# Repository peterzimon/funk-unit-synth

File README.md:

# Shmøergh Funk Live One — 6 voice paraphonic synthesizer

Shmøergh Funk Live One is a 6 voice (mostly) digitally controlled paraphonic
analog synthesizer. Its purposefully built with limitations so it's great for
live performances with quick changes in settings without presets or menu diving. It
has a lot of simple but effective ways to modulate the filter cutoff which makes
it great for funk performances. Because of its simplicity it's also cool to get
started with synthesis.

**Status:** WORK IN PROGRESS

**Latest version:** 1.1

## Features

- 6 voices (DCOs) controlled by a Raspberry Pi Pico
- Sawtooth, square, narrow pulse and fixed rate pulse with modulated square waveforms
- Analog signal path
- External filter connection with selectable various modulation sources (envelope, velocity, analog LFO, modwheel, keyboard tracking). Steiner-Parker
filter schematics and PCB is included
- 12bit digital ADSR with simplified envelope controls
- Built-in analog VCA with optional external VCA connections
- Monophonic, 3-voice unison with detune and 6-voice paraphonic modes
- MIDI input
- Eurorack compatible PCB sizing

Note: schematics does not include power supply

## References

- [Polykit DCO design](https://github.com/polykit/pico-dco)
- [The design of the Roland Juno synthesizes](https://blog.thea.codes/the-design-of-the-juno-dco/)
- [Steiner-Parker Filter](https://yusynth.net/Modular/EN/STEINERVCF/index-v2.html)

## License & info

Version: 1.1.0
Author: Peter Zimon
Copyright: 2023
Licence: MIT

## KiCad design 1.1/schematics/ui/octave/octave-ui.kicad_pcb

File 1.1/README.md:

# V1.1

- Added DC blocking to mixer inputs to avoid shifting waveforms by f=0Hz frequency DCOs
- Decreased sawtooth and square mixer amplification to avoid distortion

## License & info

Version: 1.0.0
Author: Peter Zimon
Copyright: 2023
Licence: MIT

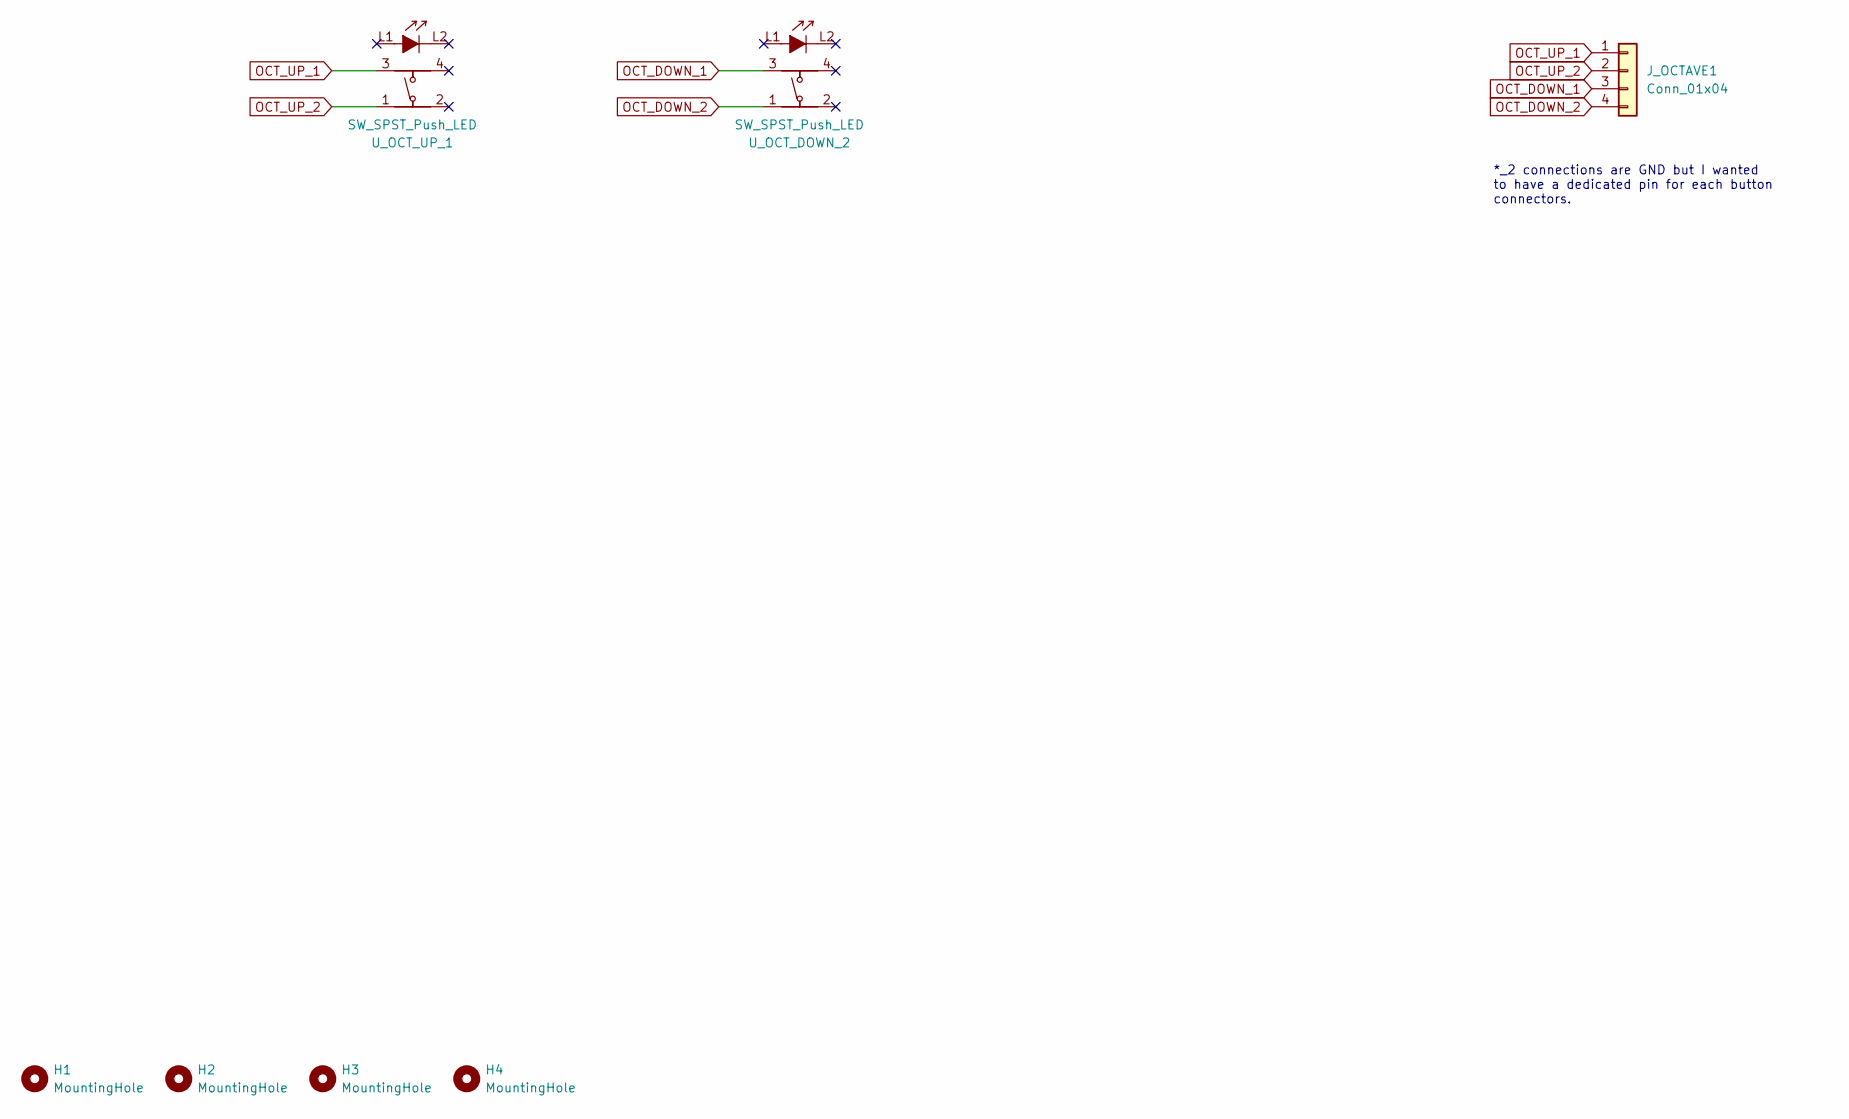
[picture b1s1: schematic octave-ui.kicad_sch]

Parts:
H1, H2, H3, H4: MountingHole; MountingHole_4mm
J_OCTAVE1: Conn_01x04; NSL25_01x04_Vertical
U_OCT_DOWN_2: SW_SPST_Push_LED; SPST_Narrow_Circular_Pushbutton_LED
U_OCT_UP_1: SW_SPST_Push_LED; SPST_Narrow_Circular_Pushbutton_LED

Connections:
OCT_DOWN_1: J_OCTAVE1.3, U_OCT_DOWN_2.3
OCT_DOWN_2: J_OCTAVE1.4, U_OCT_DOWN_2.1
OCT_UP_1: J_OCTAVE1.1, U_OCT_UP_1.3
OCT_UP_2: J_OCTAVE1.2, U_OCT_UP_1.1

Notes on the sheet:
*_2 connections are GND but I wanted to have a dedicated pin for each button connectors.

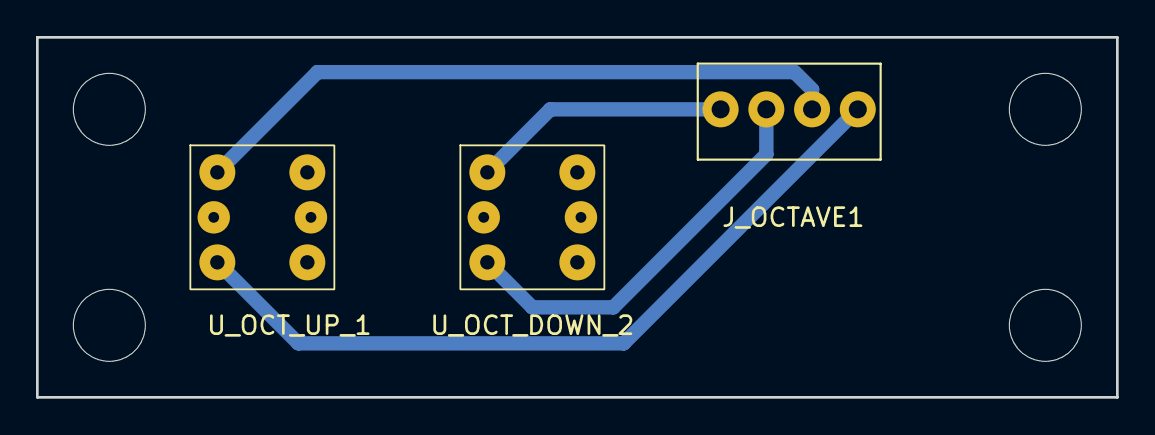
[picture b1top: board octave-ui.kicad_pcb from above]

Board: 2 copper layers, 60.0 x 20.0 mm, 7 parts (0 on the bottom side), 4 nets.

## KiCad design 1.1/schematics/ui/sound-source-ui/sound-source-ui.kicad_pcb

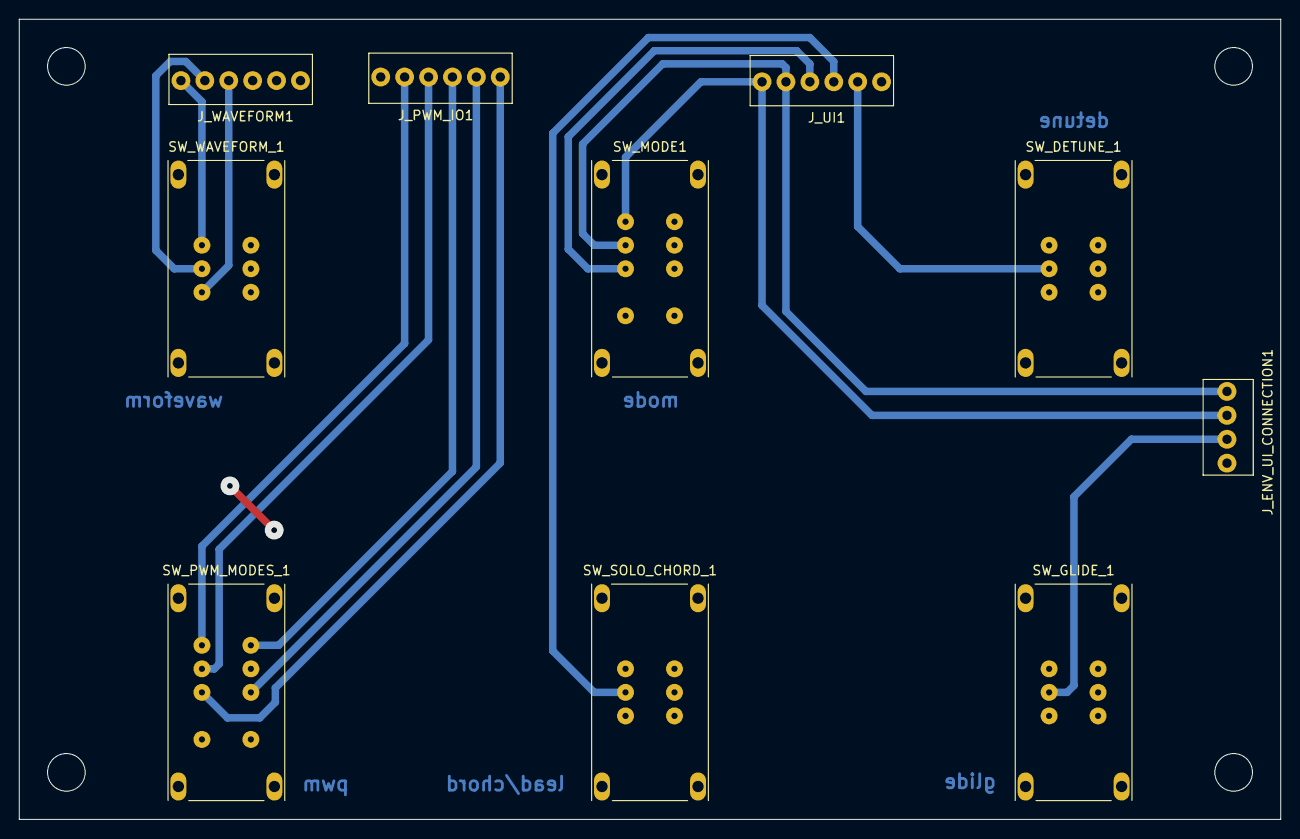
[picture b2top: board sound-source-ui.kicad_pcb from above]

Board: 2 copper layers, 134.0 x 85.0 mm, 14 parts (0 on the bottom side), 15 nets.

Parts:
H1, H2, H3, H4: MountingHole; MountingHole_4mm
J_ENV_UI_CONNECTION1: Conn_01x04; NSL25_01x04_Vertical
J_PWM_IO1: Conn_01x06; NSL25_01x06_Vertical
J_UI1: Conn_01x06; NSL25_01x06_Vertical
J_WAVEFORM1: Conn_01x03; NSL25_01x06_Vertical
SW_DETUNE_1: SW_DPDT_x2; DPDT Korg Style Switch
SW_GLIDE_1: SW_DPDT_x2; DPDT Korg Style Switch
SW_MODE1: SW_DP3T; DP3T Korg Style Switch
SW_PWM_MODES_1: SW_DP3T; DP3T Korg Style Switch
SW_SOLO_CHORD_1: SW_DPDT_x2; DPDT Korg Style Switch
SW_WAVEFORM_1: SW_DPDT_x2; DPDT Korg Style Switch

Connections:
1.5V: J_ENV_UI_CONNECTION1.1, J_UI1.2, SW_MODE1.2
+3.3V: J_ENV_UI_CONNECTION1.2, J_UI1.1, SW_MODE1.1
DETUNE: J_UI1.5, SW_DETUNE_1.3 (B)
GLIDE: J_ENV_UI_CONNECTION1.3, SW_GLIDE_1.3 (B)
GND: J_ENV_UI_CONNECTION1.4, J_PWM_IO1.6, J_UI1.6, SW_DETUNE_1.5 (C), SW_GLIDE_1.5 (C), SW_MODE1.4, SW_PWM_MODES_1.4, SW_PWM_MODES_1.6, SW_PWM_MODES_1.8, SW_SOLO_CHORD_1.5 (C)
MODE: J_UI1.3, SW_MODE1.3
PULSE_WIDTH: J_PWM_IO1.1, SW_PWM_MODES_1.3
PWM_LFO: J_PWM_IO1.3, SW_PWM_MODES_1.5
PWM_LFO_BIAS: J_PWM_IO1.5, SW_PWM_MODES_1.1
PWM_NARROW_BIAS: J_PWM_IO1.4, SW_PWM_MODES_1.2
PWM_OUT: J_PWM_IO1.2, SW_PWM_MODES_1.7
SAW_IN: J_WAVEFORM1.3, SW_WAVEFORM_1.5 (C)
SOLO_CHORD: J_UI1.4, SW_SOLO_CHORD_1.3 (B)
SQR_IN: J_WAVEFORM1.1, SW_WAVEFORM_1.1 (A)
WAVEFORM_OUT: J_WAVEFORM1.2, SW_WAVEFORM_1.3 (B)

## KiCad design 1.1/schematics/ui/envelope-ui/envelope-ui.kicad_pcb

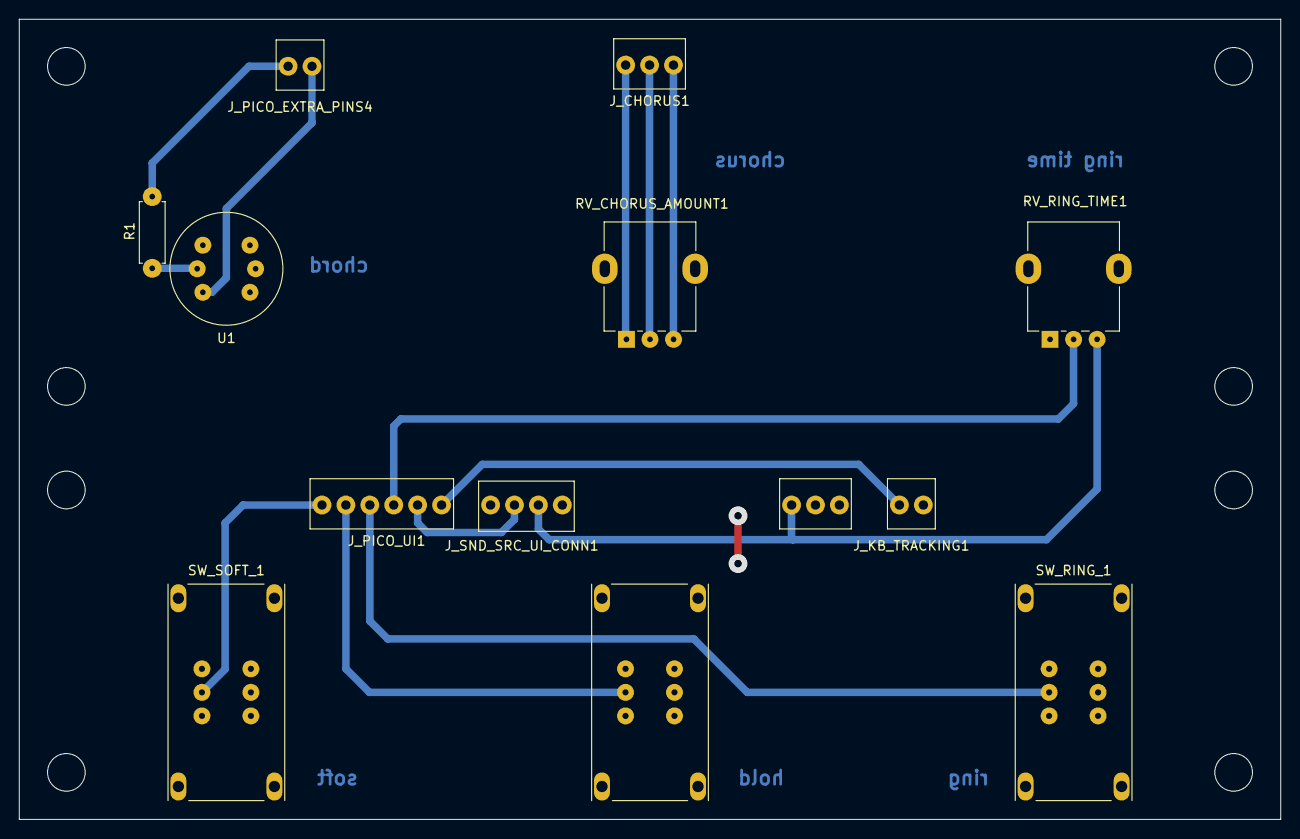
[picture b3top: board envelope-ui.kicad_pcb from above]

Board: 2 copper layers, 134.0 x 85.0 mm, 21 parts (0 on the bottom side), 14 nets.

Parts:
H1, H2, H3, H4, H5, H6, H7, H8: MountingHole; MountingHole_4mm
J_CHORUS1: Conn_01x03; NSL25_01x03_Vertical
J_KB_TRACKING1: Conn_01x02; NSL25_01x02_Vertical
J_PICO_EXTRA_PINS4: Conn_01x02; NSL25_01x02_Vertical
J_PICO_UI1: Conn_01x06; NSL25_01x06_Vertical
J_PWR1: Conn_01x03; NSL25_01x03_Vertical
J_SND_SRC_UI_CONN1: Conn_01x04; NSL25_01x04_Vertical
R1: R; R_Axial_DIN0207_L6.3mm_D2.5mm_P7.62mm_Horizontal
RV_CHORUS_AMOUNT1: 100k; Potentiometer_Alpha_RD901F-40-00D_Single_Vertical
RV_RING_TIME1: 100k; Potentiometer_Alpha_RD901F-40-00D_Single_Vertical
SW_HOLD_1: SW_DPDT_x2; DPDT Korg Style Switch
SW_RING_1: SW_DPDT_x2; DPDT Korg Style Switch
SW_SOFT_1: SW_DPDT_x2; DPDT Korg Style Switch
U1: SW_SPST_Push_LED; SPST_Circular_Pushbutton_LED

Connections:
+3.3V: J_PWR1.1, J_SND_SRC_UI_CONN1.2, RV_RING_TIME1.3
CHORD_BTN: J_PICO_EXTRA_PINS4.2, U1.3
CHORD_LED: J_PICO_EXTRA_PINS4.1, R1.1
CHORUS_1: J_CHORUS1.1, RV_CHORUS_AMOUNT1.1
CHORUS_2: J_CHORUS1.2, RV_CHORUS_AMOUNT1.2
CHORUS_3: J_CHORUS1.3, RV_CHORUS_AMOUNT1.3
GLIDE: J_PICO_UI1.5, J_SND_SRC_UI_CONN1.3
GND: J_KB_TRACKING1.2, J_PWR1.2, J_PWR1.3, J_SND_SRC_UI_CONN1.4, RV_RING_TIME1.1, SW_HOLD_1.5 (C), SW_RING_1.5 (C), SW_SOFT_1.5 (C), U1.1, U1.L2
HOLD: J_PICO_UI1.2, SW_HOLD_1.3 (B)
KB_TRACKING: J_KB_TRACKING1.1, J_PICO_UI1.6
unnamed: R1.2, U1.L1
RING: J_PICO_UI1.3, SW_RING_1.3 (B)
RING_TIME: J_PICO_UI1.4, RV_RING_TIME1.2
SOFT: J_PICO_UI1.1, SW_SOFT_1.3 (B)

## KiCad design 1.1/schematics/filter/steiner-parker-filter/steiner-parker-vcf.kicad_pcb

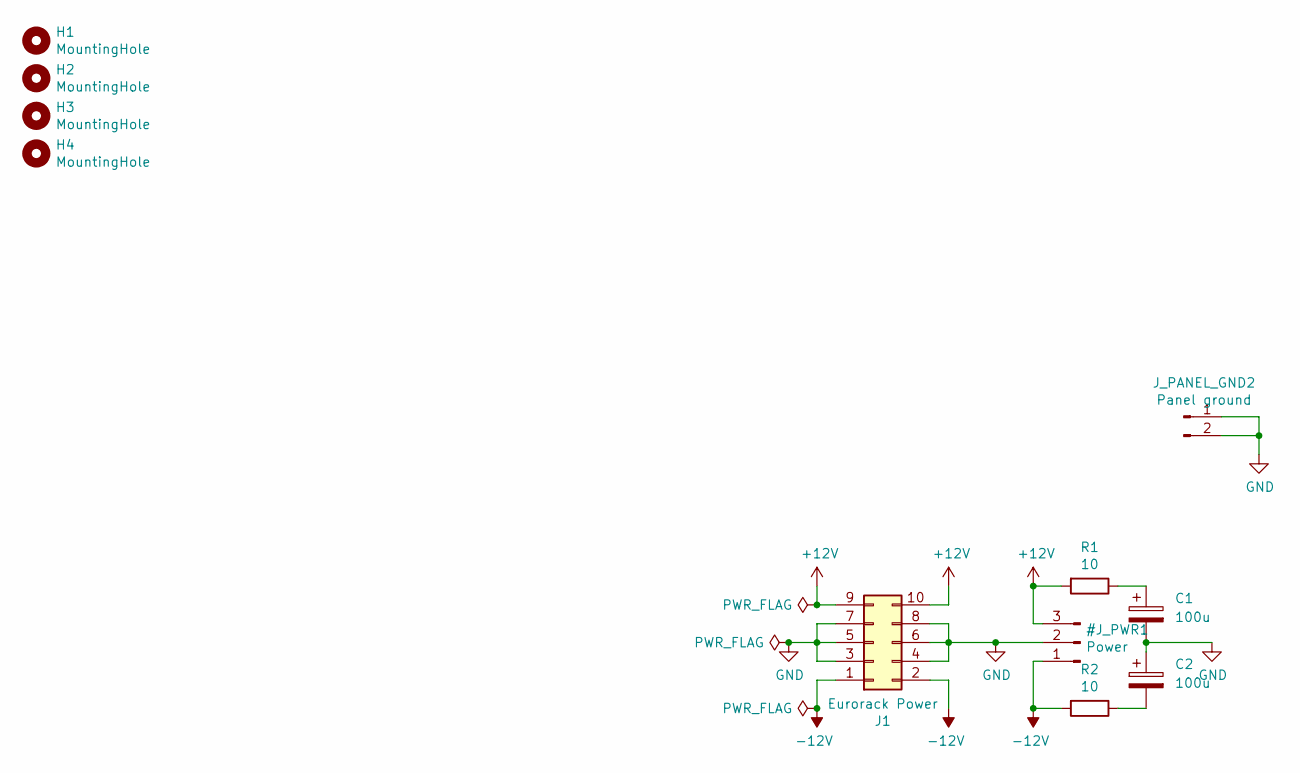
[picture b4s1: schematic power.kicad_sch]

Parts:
C1, C2: 100u; CP_Radial_D6.3mm_P2.50mm
H1, H2, H3, H4: MountingHole; MountingHole_3mm_Pad
J1: Eurorack Power; IDC-Header_2x05_P2.54mm_Vertical
J_PANEL_GND2: Panel ground; NSL25_01x02_Vertical
R1, R2: 10; R_Axial_DIN0207_L6.3mm_D2.5mm_P7.62mm_Horizontal

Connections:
unnamed: C1.1, R1.1
unnamed: C2.2, R2.1

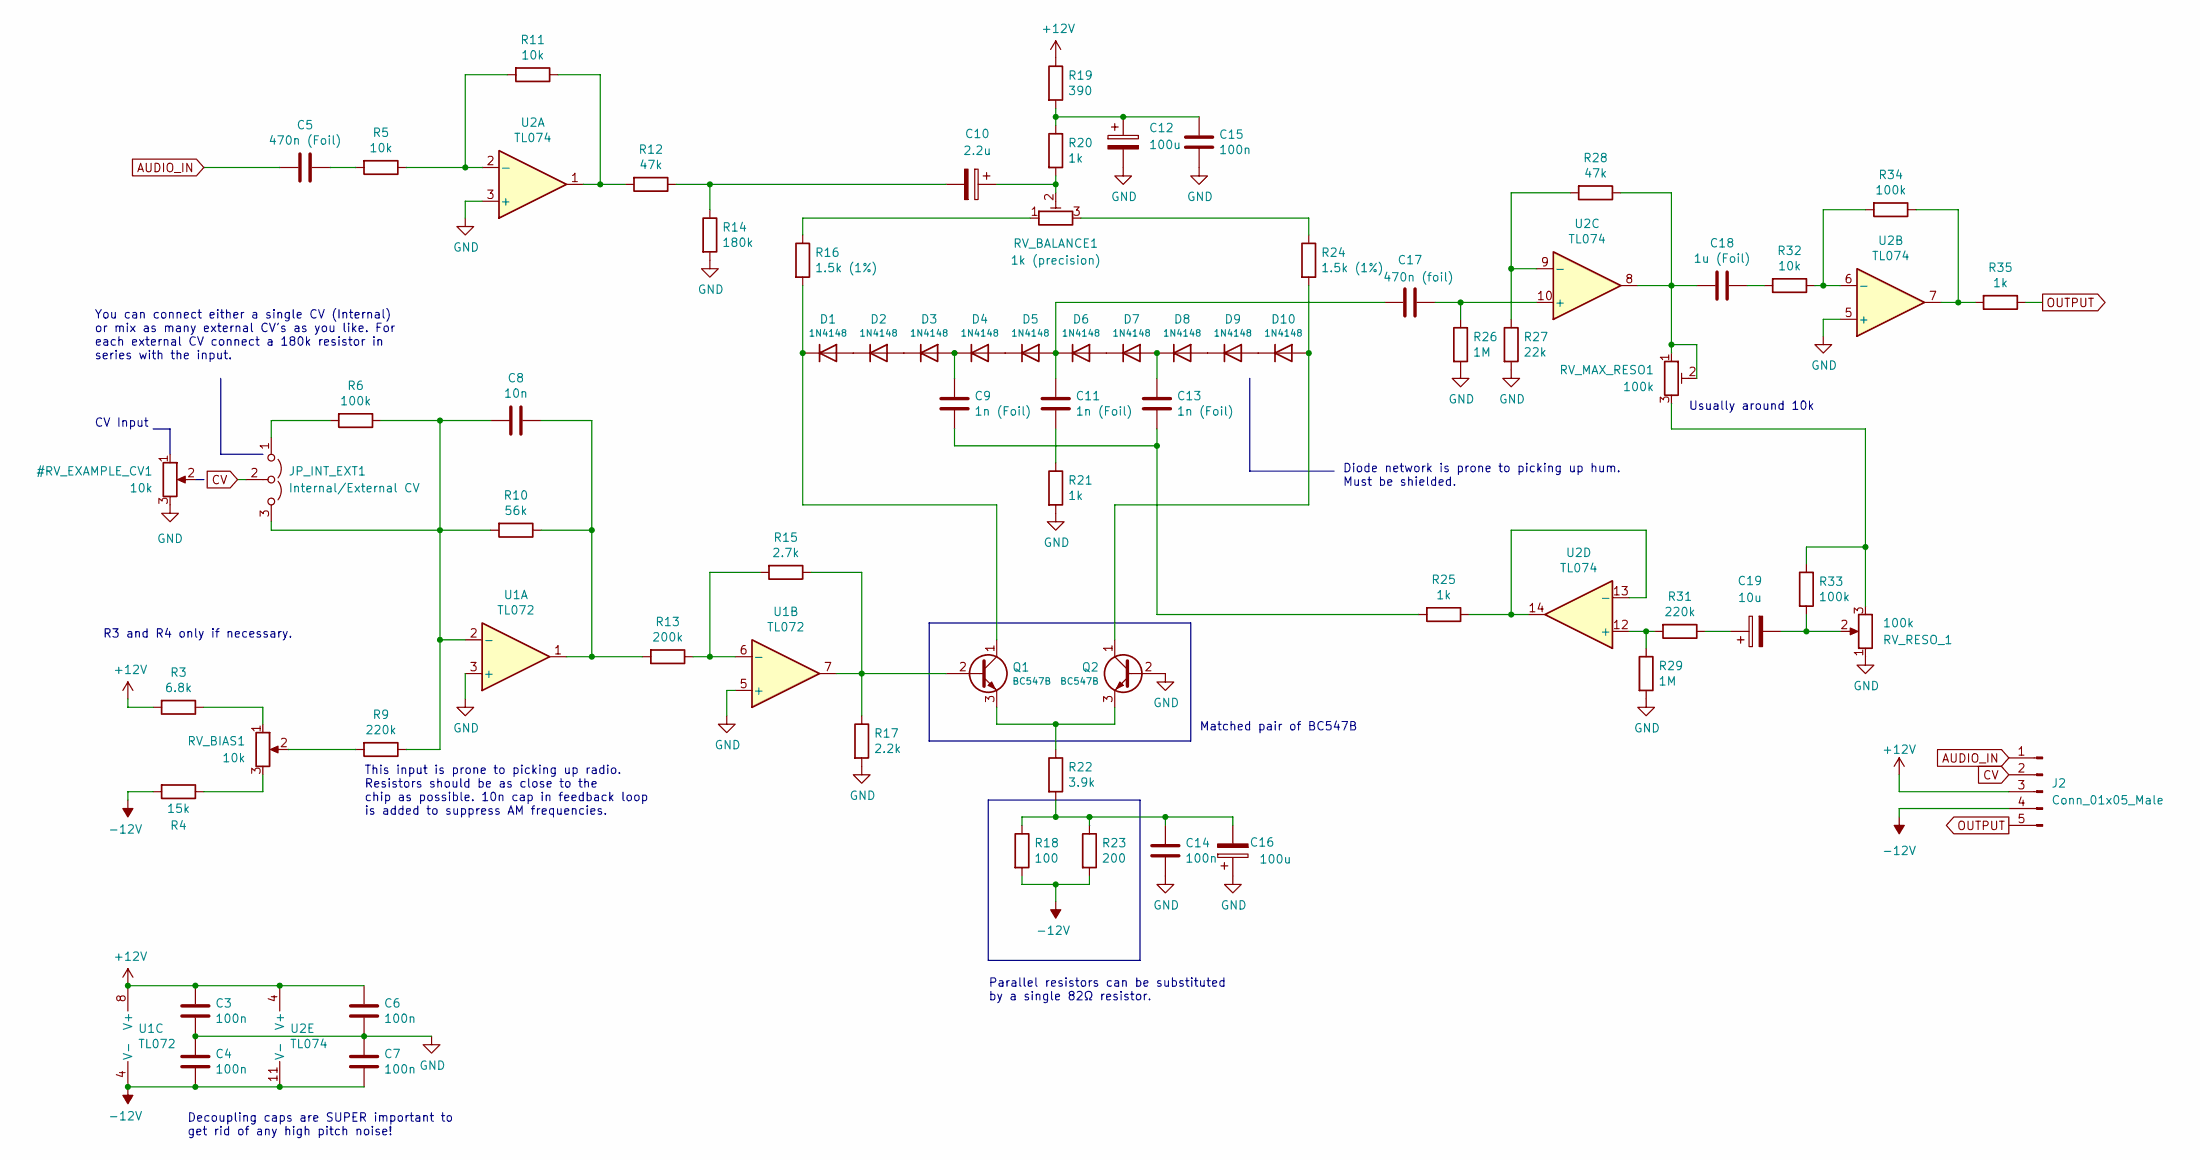
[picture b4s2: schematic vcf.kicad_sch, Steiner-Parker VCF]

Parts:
C3, C4, C6, C7, C14, C15: 100n; C_Disc_D3.0mm_W2.0mm_P2.50mm
C5: 470n (Foil); C_Rect_L7.0mm_W2.5mm_P5.00mm
C8: 10n; C_Disc_D3.0mm_W2.0mm_P2.50mm
C9, C11, C13: 1n (Foil); C_Rect_L7.0mm_W2.5mm_P5.00mm
C10: 2.2u; CP_Radial_D6.3mm_P2.50mm
C12, C16: 100u; CP_Radial_D6.3mm_P2.50mm
C17: 470n (foil); C_Rect_L7.0mm_W2.5mm_P5.00mm
C18: 1u (Foil); C_Rect_L7.0mm_W4.5mm_P5.00mm
C19: 10u; CP_Radial_D6.3mm_P2.50mm
D1, D2, D3, D4, D5, D6, D7, D8, D9, D10: 1N4148; D_DO-35_SOD27_P7.62mm_Horizontal
J2: Conn_01x05_Male; NSL25_01x05_Vertical
JP_INT_EXT1: Internal/External CV; PinSocket_1x03_P2.54mm_Vertical
Q1, Q2: BC547B; TO-92_Inline_Wide
R3: 6.8k; R_Axial_DIN0207_L6.3mm_D2.5mm_P7.62mm_Horizontal
R4: 15k; R_Axial_DIN0207_L6.3mm_D2.5mm_P7.62mm_Horizontal
R5, R11, R32: 10k; R_Axial_DIN0207_L6.3mm_D2.5mm_P7.62mm_Horizontal
R6, R33, R34: 100k; R_Axial_DIN0207_L6.3mm_D2.5mm_P7.62mm_Horizontal
R9, R31: 220k; R_Axial_DIN0207_L6.3mm_D2.5mm_P7.62mm_Horizontal
R10: 56k; R_Axial_DIN0207_L6.3mm_D2.5mm_P7.62mm_Horizontal
R12, R28: 47k; R_Axial_DIN0207_L6.3mm_D2.5mm_P7.62mm_Horizontal
R13: 200k; R_Axial_DIN0207_L6.3mm_D2.5mm_P7.62mm_Horizontal
R14: 180k; R_Axial_DIN0207_L6.3mm_D2.5mm_P7.62mm_Horizontal
R15: 2.7k; R_Axial_DIN0207_L6.3mm_D2.5mm_P7.62mm_Horizontal
R16, R24: 1.5k (1%); R_Axial_DIN0207_L6.3mm_D2.5mm_P7.62mm_Horizontal
R17: 2.2k; R_Axial_DIN0207_L6.3mm_D2.5mm_P7.62mm_Horizontal
R18: 100; R_Axial_DIN0207_L6.3mm_D2.5mm_P7.62mm_Horizontal
R19: 390; R_Axial_DIN0207_L6.3mm_D2.5mm_P7.62mm_Horizontal
R20, R21, R25, R35: 1k; R_Axial_DIN0207_L6.3mm_D2.5mm_P7.62mm_Horizontal
R22: 3.9k; R_Axial_DIN0207_L6.3mm_D2.5mm_P7.62mm_Horizontal
R23: 200; R_Axial_DIN0207_L6.3mm_D2.5mm_P7.62mm_Horizontal
R26, R29: 1M; R_Axial_DIN0207_L6.3mm_D2.5mm_P7.62mm_Horizontal
R27: 22k; R_Axial_DIN0207_L6.3mm_D2.5mm_P7.62mm_Horizontal
RV_BALANCE1: 1k (precision); Potentiometer_Bourns_3296W_Vertical
RV_BIAS1: 10k; Potentiometer_Runtron_RM-065_Vertical
RV_MAX_RESO1: 100k; Potentiometer_Runtron_RM-065_Vertical
RV_RESO_1: 100k; NSL25_01x03_Vertical
U1: TL072; DIP-8_W7.62mm_LongPads
U2: TL074; DIP-14_W7.62mm_LongPads

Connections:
AUDIO_IN: C5.2, J2.1
CV: J2.2, JP_INT_EXT1.2 (C)
unnamed: C5.1, R5.2
unnamed: C8.1, R10.1, R13.2, U1.1
unnamed: C10.1, R20.2, RV_BALANCE1.2
unnamed: C10.2, R12.1, R14.1
unnamed: C11.2, R21.1
unnamed: C12.1, C15.1, R19.2, R20.1
unnamed: C9.2, C13.2, R25.2
unnamed: C14.1, C16.2, R18.1, R22.2, R23.1
unnamed: C18.1, R32.2
unnamed: C18.2, R28.1, RV_MAX_RESO1.1, RV_MAX_RESO1.2, U2.8
unnamed: C19.1, R31.1
unnamed: C19.2, R33.2, RV_RESO_1.2
unnamed: D1.2 (A), D2.1 (K)
unnamed: D1.1 (K), Q1.1 (C), R16.2
unnamed: D2.2 (A), D3.1 (K)
unnamed: C9.1, D3.2 (A), D4.1 (K)
unnamed: D4.2 (A), D5.1 (K)
unnamed: C11.1, C17.2, D5.2 (A), D6.1 (K)
unnamed: D6.2 (A), D7.1 (K)
unnamed: C13.1, D7.2 (A), D8.1 (K)
unnamed: D8.2 (A), D9.1 (K)
unnamed: D10.2 (A), Q2.1 (C), R24.2
unnamed: D9.2 (A), D10.1 (K)
unnamed: JP_INT_EXT1.1 (A), R6.2
unnamed: C8.2, JP_INT_EXT1.3 (B), R6.1, R9.1, R10.2, U1.2 (-)
unnamed: Q1.2 (B), R15.1, R17.1, U1.7
unnamed: Q1.3 (E), Q2.3 (E), R22.1
unnamed: R3.1, RV_BIAS1.1
unnamed: R4.1, RV_BIAS1.3
unnamed: R9.2, RV_BIAS1.2
unnamed: R11.1, R12.2, U2.1
unnamed: R16.1, RV_BALANCE1.1
unnamed: R24.1, RV_BALANCE1.3
unnamed: R33.1, RV_MAX_RESO1.3, RV_RESO_1.3
unnamed: R34.1, R35.2, U2.7
unnamed: R13.1, R15.2, U1.6 (-)
unnamed: R5.1, R11.2, U2.2 (-)
unnamed: R32.1, R34.2, U2.6 (-)
unnamed: C17.1, R26.1, U2.10 (+)
unnamed: R27.1, R28.2, U2.9 (-)
unnamed: R29.1, R31.2, U2.12 (+)
unnamed: R25.1, U2.13 (-), U2.14
OUTPUT: J2.5, R35.1

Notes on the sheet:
CV Input
This input is prone to picking up radio. Resistors should be as close to the chip as possible. 10n cap in feedback loop is added to suppress AM frequencies.
Decoupling caps are SUPER important to get rid of any high pitch noise!
Matched pair of BC547B
R3 and R4 only if necessary.
Parallel resistors can be substituted by a single 82Ω resistor.
Usually around 10k
You can connect either a single CV (Internal) or mix as many external CV's as you like. For each external CV connect a 180k resistor in series with the input.
Diode network is prone to picking up hum. Must be shielded.

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
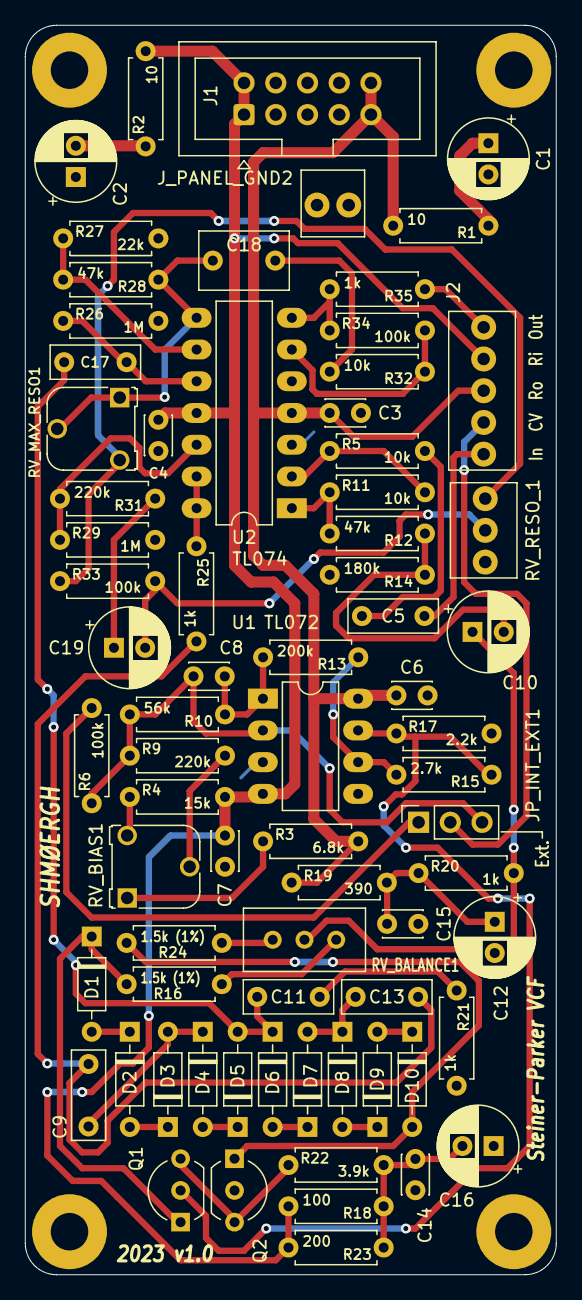
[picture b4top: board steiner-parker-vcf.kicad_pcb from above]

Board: 2 copper layers, 42.5 x 100.0 mm, 77 parts (0 on the bottom side), 50 nets.

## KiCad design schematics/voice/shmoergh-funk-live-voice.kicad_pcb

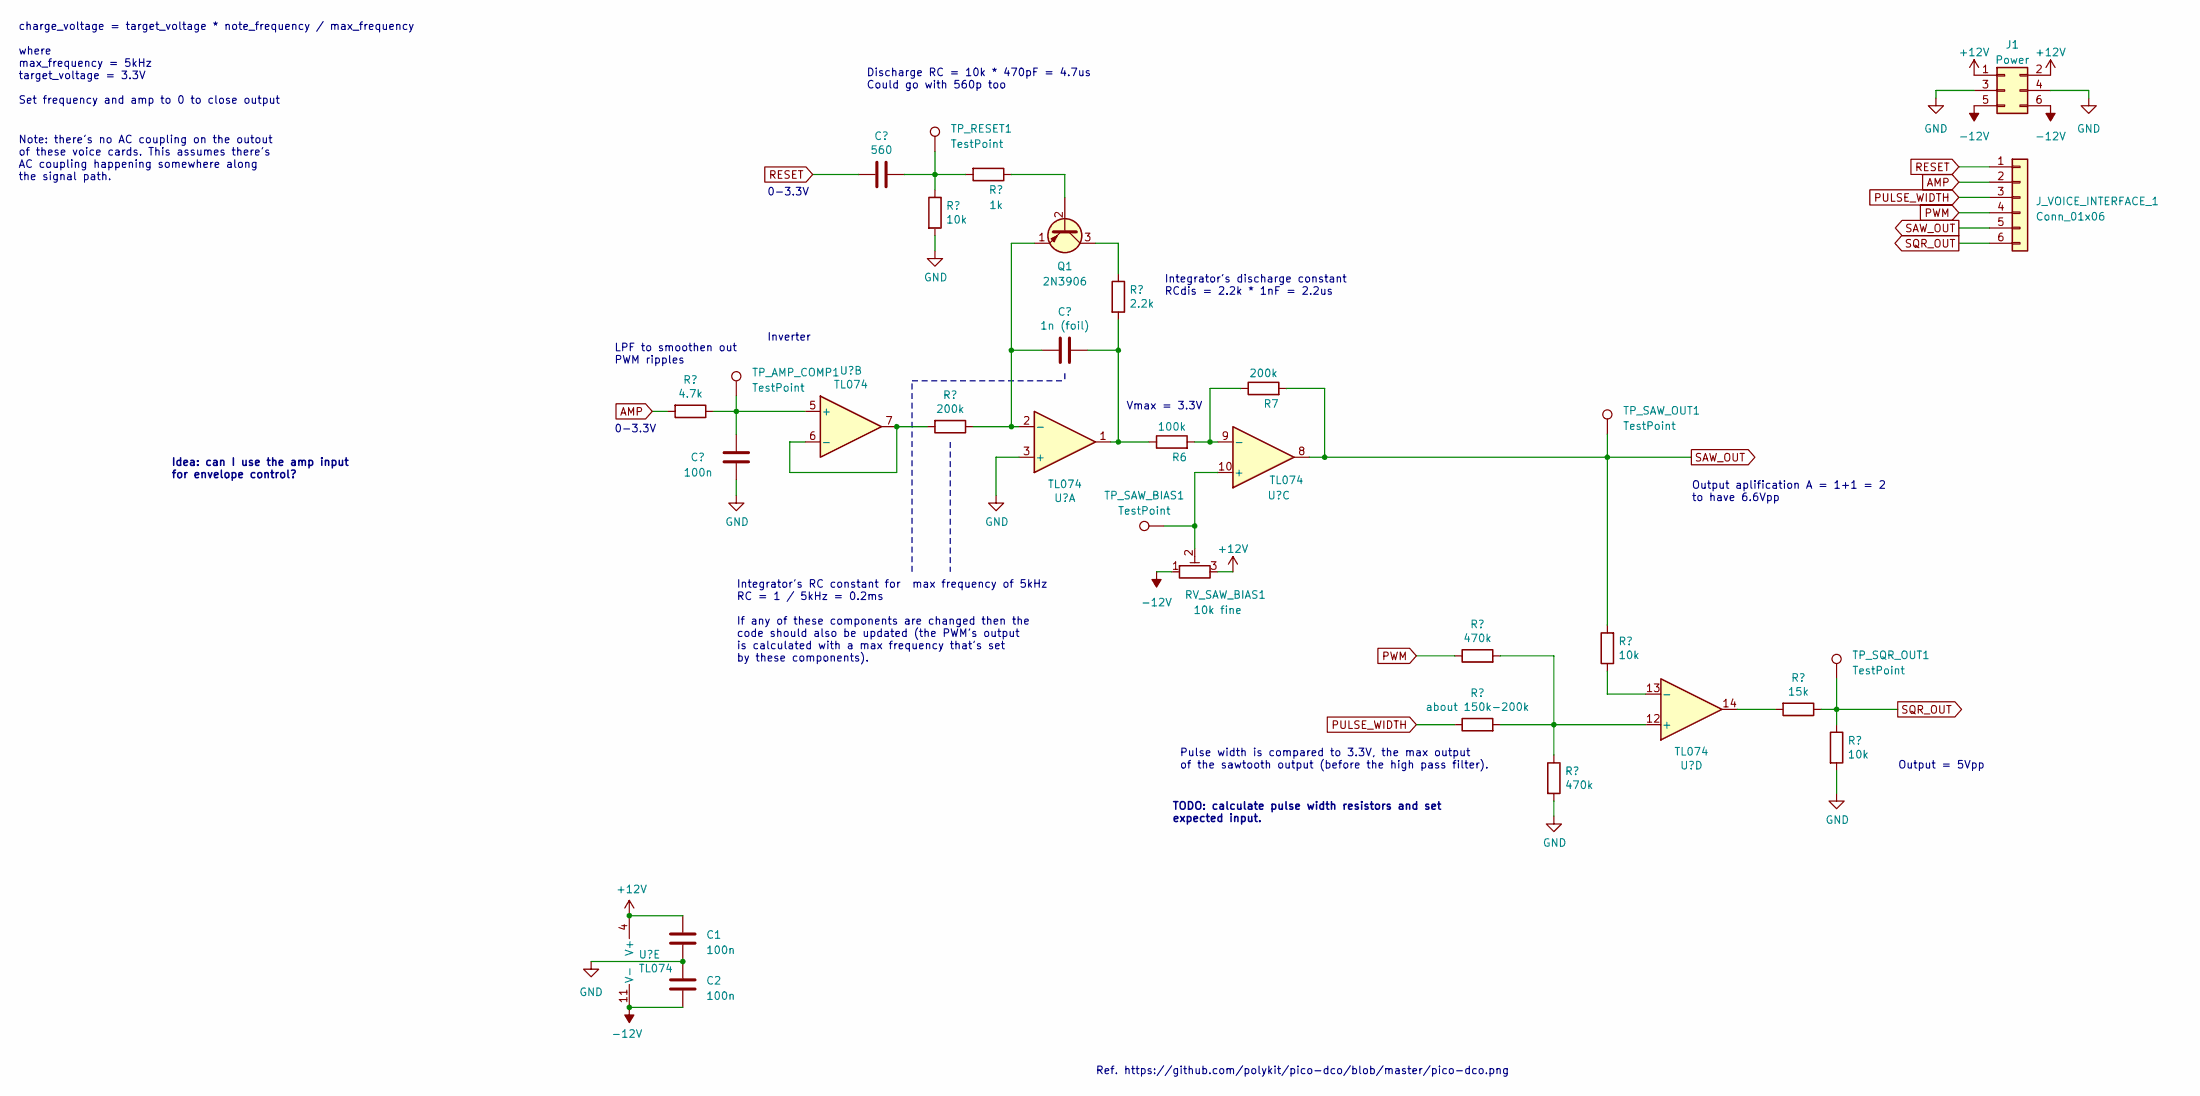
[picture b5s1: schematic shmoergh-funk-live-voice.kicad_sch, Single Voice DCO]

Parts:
C1, C2, C3: 100n; C_Disc_D3.4mm_W2.1mm_P2.50mm
C4: 560; C_Disc_D3.4mm_W2.1mm_P2.50mm
C5: 1n (foil); C_Rect_L7.2mm_W4.5mm_P5.00mm_FKS2_FKP2_MKS2_MKP2
J1: Power; PinHeader_2x03_P2.54mm_Vertical
J_VOICE_INTERFACE_1: Conn_01x06; PinHeader_1x06_P2.54mm_Vertical
Q1: 2N3906; TO-92L_Inline_Wide
R1: 4.7k; R_Axial_DIN0207_L6.3mm_D2.5mm_P7.62mm_Horizontal
R2, R11, R13: 10k; R_Axial_DIN0207_L6.3mm_D2.5mm_P7.62mm_Horizontal
R3, R7: 200k; R_Axial_DIN0207_L6.3mm_D2.5mm_P7.62mm_Horizontal
R4: 1k; R_Axial_DIN0207_L6.3mm_D2.5mm_P7.62mm_Horizontal
R5: 2.2k; R_Axial_DIN0207_L6.3mm_D2.5mm_P7.62mm_Horizontal
R6: 100k; R_Axial_DIN0207_L6.3mm_D2.5mm_P7.62mm_Horizontal
R8, R10: 470k; R_Axial_DIN0207_L6.3mm_D2.5mm_P7.62mm_Horizontal
R9: about 150k-200k; R_Axial_DIN0207_L6.3mm_D2.5mm_P7.62mm_Horizontal
R12: 15k; R_Axial_DIN0207_L6.3mm_D2.5mm_P7.62mm_Horizontal
RV_SAW_BIAS1: 10k fine; Potentiometer_ACP_CA6-H2,5_Horizontal
TP_AMP_COMP1: TestPoint; Pin_D0.7mm_L6.5mm_W1.8mm_FlatFork
TP_RESET1: TestPoint; Pin_D0.7mm_L6.5mm_W1.8mm_FlatFork
TP_SAW_BIAS1: TestPoint; Pin_D0.7mm_L6.5mm_W1.8mm_FlatFork
TP_SAW_OUT1: TestPoint; Pin_D0.7mm_L6.5mm_W1.8mm_FlatFork
TP_SQR_OUT1: TestPoint; Pin_D0.7mm_L6.5mm_W1.8mm_FlatFork
U1: TL074; DIP-14_W7.62mm_Socket_LongPads

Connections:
+12V: C1.1, J1.1, J1.2, RV_SAW_BIAS1.3, U1.4 (V+)
-12V: C2.2, J1.5, J1.6, RV_SAW_BIAS1.1, U1.11 (V-)
AMP: J_VOICE_INTERFACE_1.2, R1.2
GND: C1.2, C2.1, C3.2, J1.3, J1.4, R2.2, R10.2, R13.2, U1.3 (+)
unnamed: C4.1, R2.1, R4.2, TP_RESET1.1
unnamed: C5.1, R5.2, R6.1, U1.1
unnamed: Q1.2 (B), R4.1
unnamed: Q1.3 (C), R5.1
unnamed: C5.2, Q1.1 (E), R3.1, U1.2 (-)
unnamed: R12.2, U1.14
unnamed: C3.1, R1.1, TP_AMP_COMP1.1, U1.5 (+)
unnamed: R3.2, U1.6 (-), U1.7
unnamed: RV_SAW_BIAS1.2, TP_SAW_BIAS1.1, U1.10 (+)
unnamed: R6.2, R7.1, U1.9 (-)
unnamed: R8.2, R9.2, R10.1, U1.12 (+)
unnamed: R11.1, U1.13 (-)
PULSE_WIDTH: J_VOICE_INTERFACE_1.3, R9.1
PWM: J_VOICE_INTERFACE_1.4, R8.1
RESET: C4.2, J_VOICE_INTERFACE_1.1
SAW_OUT: J_VOICE_INTERFACE_1.5, R7.2, R11.2, TP_SAW_OUT1.1, U1.8
SQR_OUT: J_VOICE_INTERFACE_1.6, R12.1, R13.1, TP_SQR_OUT1.1

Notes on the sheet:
Pulse width is compared to 3.3V, the max output of the sawtooth output (before the high pass filter).
Inverter
Idea: can I use the amp input for envelope control?
Vmax = 3.3V
TODO: calculate pulse width resistors and set expected input.
Output = 5Vpp
0-3.3V
charge_voltage = target_voltage * note_frequency / max_frequency where max_frequency = 5kHz target_voltage = 3.3V Set frequency and amp to 0 to close output
Output aplification A = 1+1 = 2 to have 6.6Vpp
Integrator's discharge constant RCdis = 2.2k * 1nF = 2.2us
Note: there's no AC coupling on the outout of these voice cards. This assumes there's AC coupling happening somewhere along the signal path.
LPF to smoothen out PWM ripples
Discharge RC = 10k * 470pF = 4.7us Could go with 560p too
Integrator's RC constant for max frequency of 5kHz RC = 1 / 5kHz = 0.2ms If any of these components are changed then the code should also be updated (the PWM's output is calculated with a max frequency that's set by these components).
Ref. https://github.com/polykit/pico-dco/blob/master/pico-dco.png

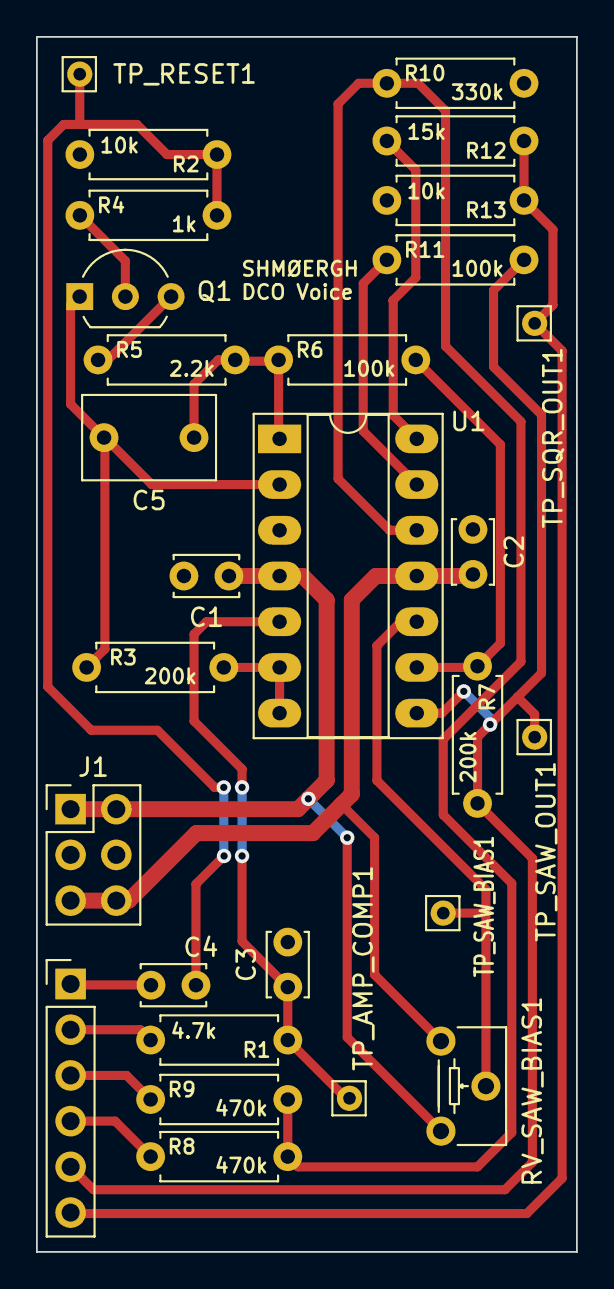
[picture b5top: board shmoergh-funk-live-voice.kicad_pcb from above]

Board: 2 copper layers, 30.0 x 67.5 mm, 28 parts (0 on the bottom side), 21 nets.

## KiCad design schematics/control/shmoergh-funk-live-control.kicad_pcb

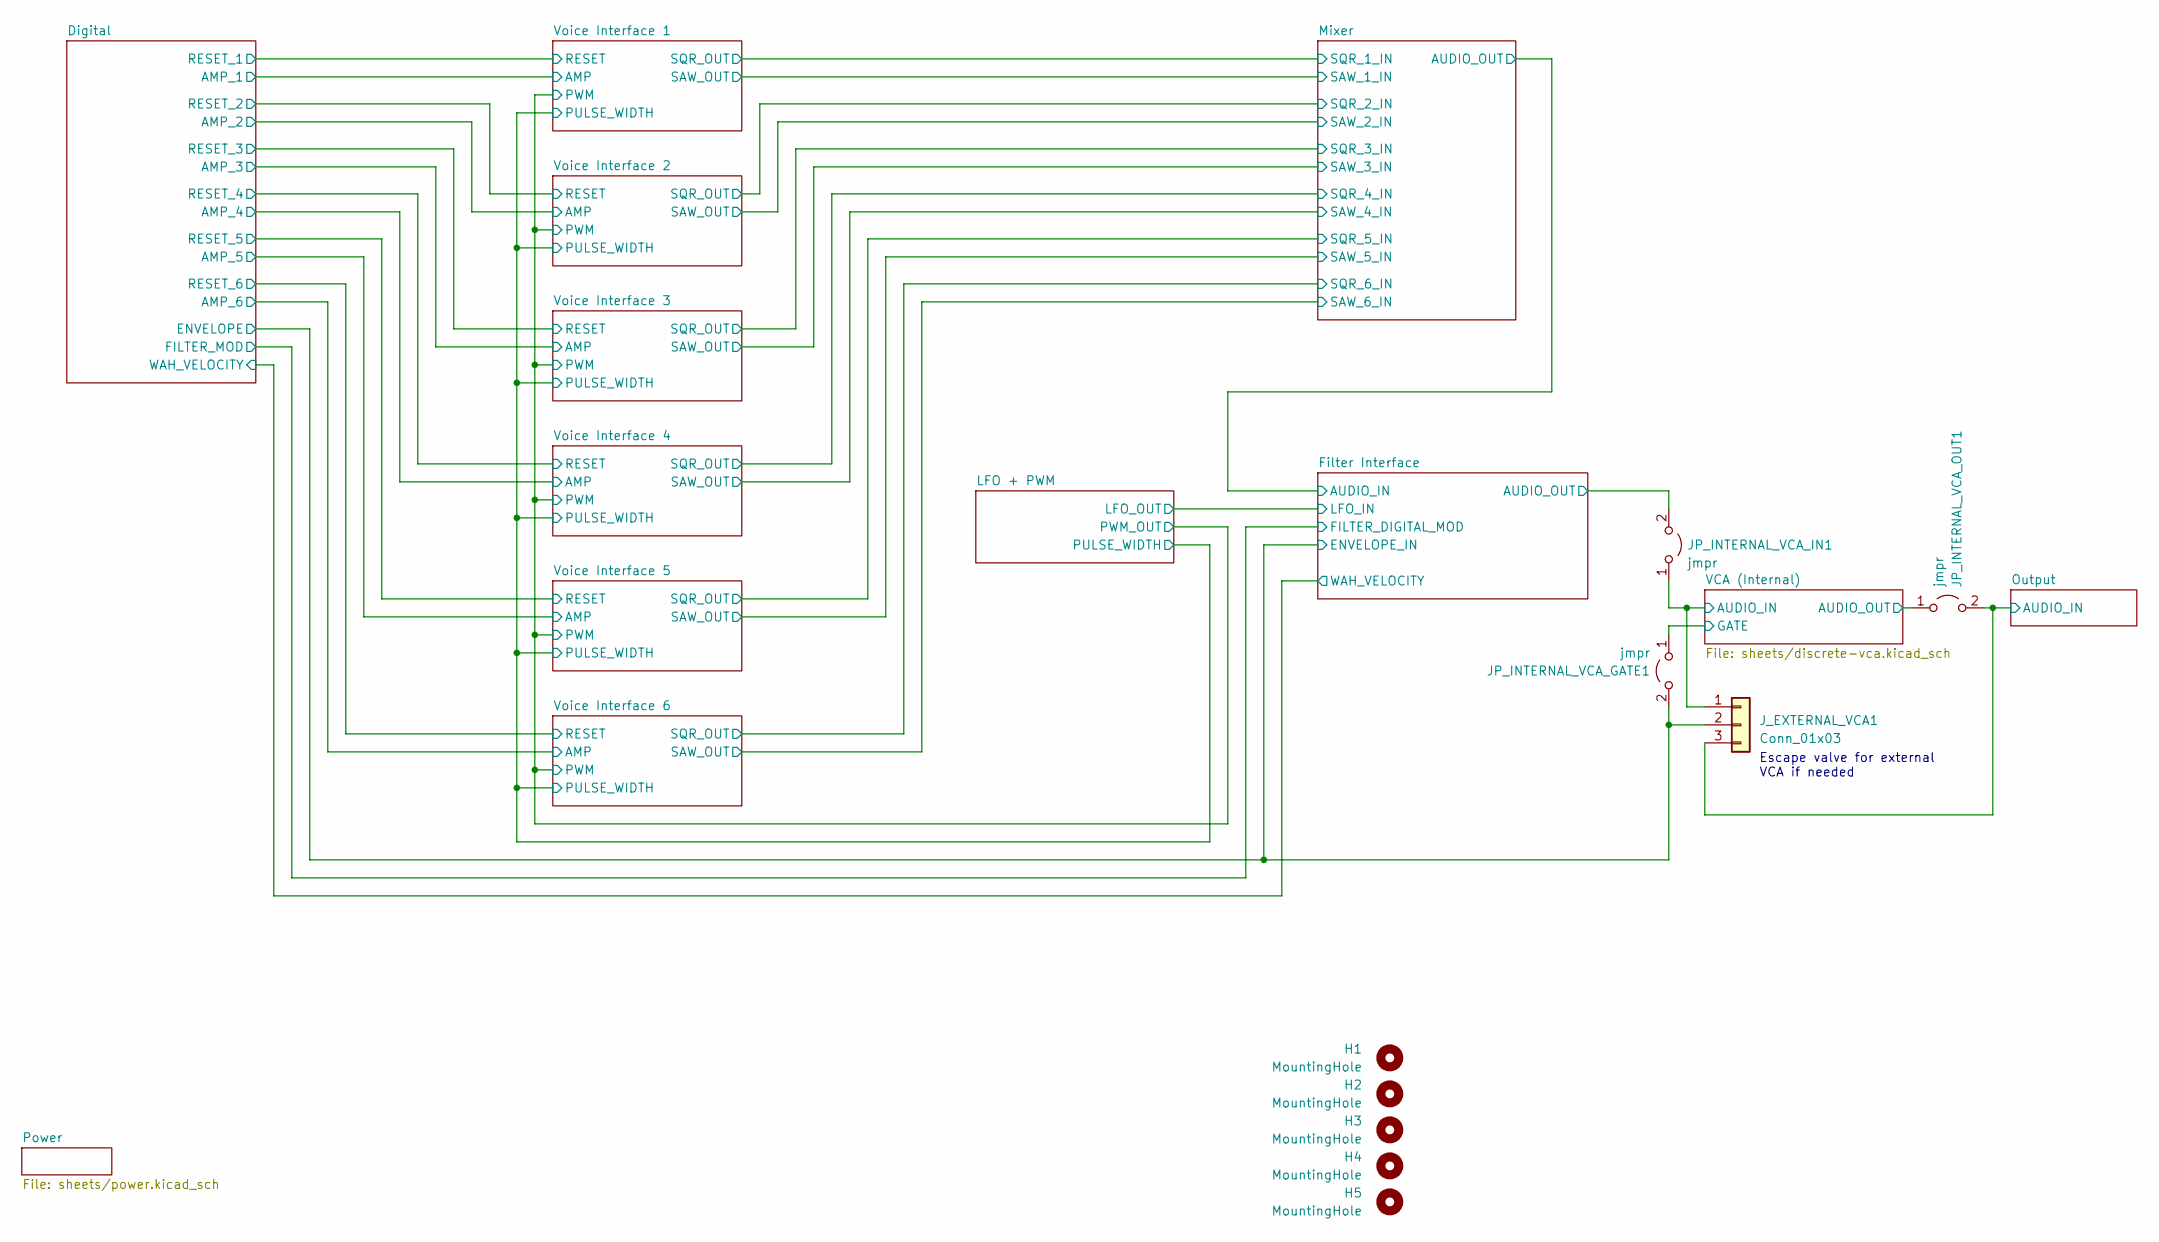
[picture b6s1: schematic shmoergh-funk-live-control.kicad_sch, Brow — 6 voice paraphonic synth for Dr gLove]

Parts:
H1, H2, H3, H4, H5: MountingHole; MountingHole_3mm_Pad
JP_INTERNAL_VCA_GATE1: jmpr; Jumper_P2.54mm_D0.7mm
JP_INTERNAL_VCA_IN1: jmpr; Jumper_P2.54mm_D0.7mm
JP_INTERNAL_VCA_OUT1: jmpr; Jumper_P2.54mm_D0.7mm
J_EXTERNAL_VCA1: Conn_01x03; NSL25_01x03_Vertical

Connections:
/Filter Interface/AUDIO_OUT: JP_INTERNAL_VCA_IN1.2 (B); also elsewhere on the board
/Output/AUDIO_IN: JP_INTERNAL_VCA_OUT1.2 (B), J_EXTERNAL_VCA1.3; also elsewhere on the board
/VCA (Internal)/AUDIO_IN: JP_INTERNAL_VCA_IN1.1 (A), J_EXTERNAL_VCA1.1; also elsewhere on the board
/VCA (Internal)/AUDIO_OUT: JP_INTERNAL_VCA_OUT1.1 (A); also elsewhere on the board

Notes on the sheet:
Escape valve for external VCA if needed
